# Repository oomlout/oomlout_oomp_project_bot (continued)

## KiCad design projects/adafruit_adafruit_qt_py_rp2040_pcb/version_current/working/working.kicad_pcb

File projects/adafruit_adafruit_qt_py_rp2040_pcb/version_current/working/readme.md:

# Adafruit-QT-Py-RP2040-PCB by adafruit  
This is a harvested standardized copy of a project from github.  
The original project can be found at:  
https://github.com/adafruit/Adafruit-QT-Py-RP2040-PCB  
Please consult that link for additional, details, files, and license information.  
Note: It was auto harvested and if the original repo had more than one board file or anything out of the ordinary the files here are likely not representative.

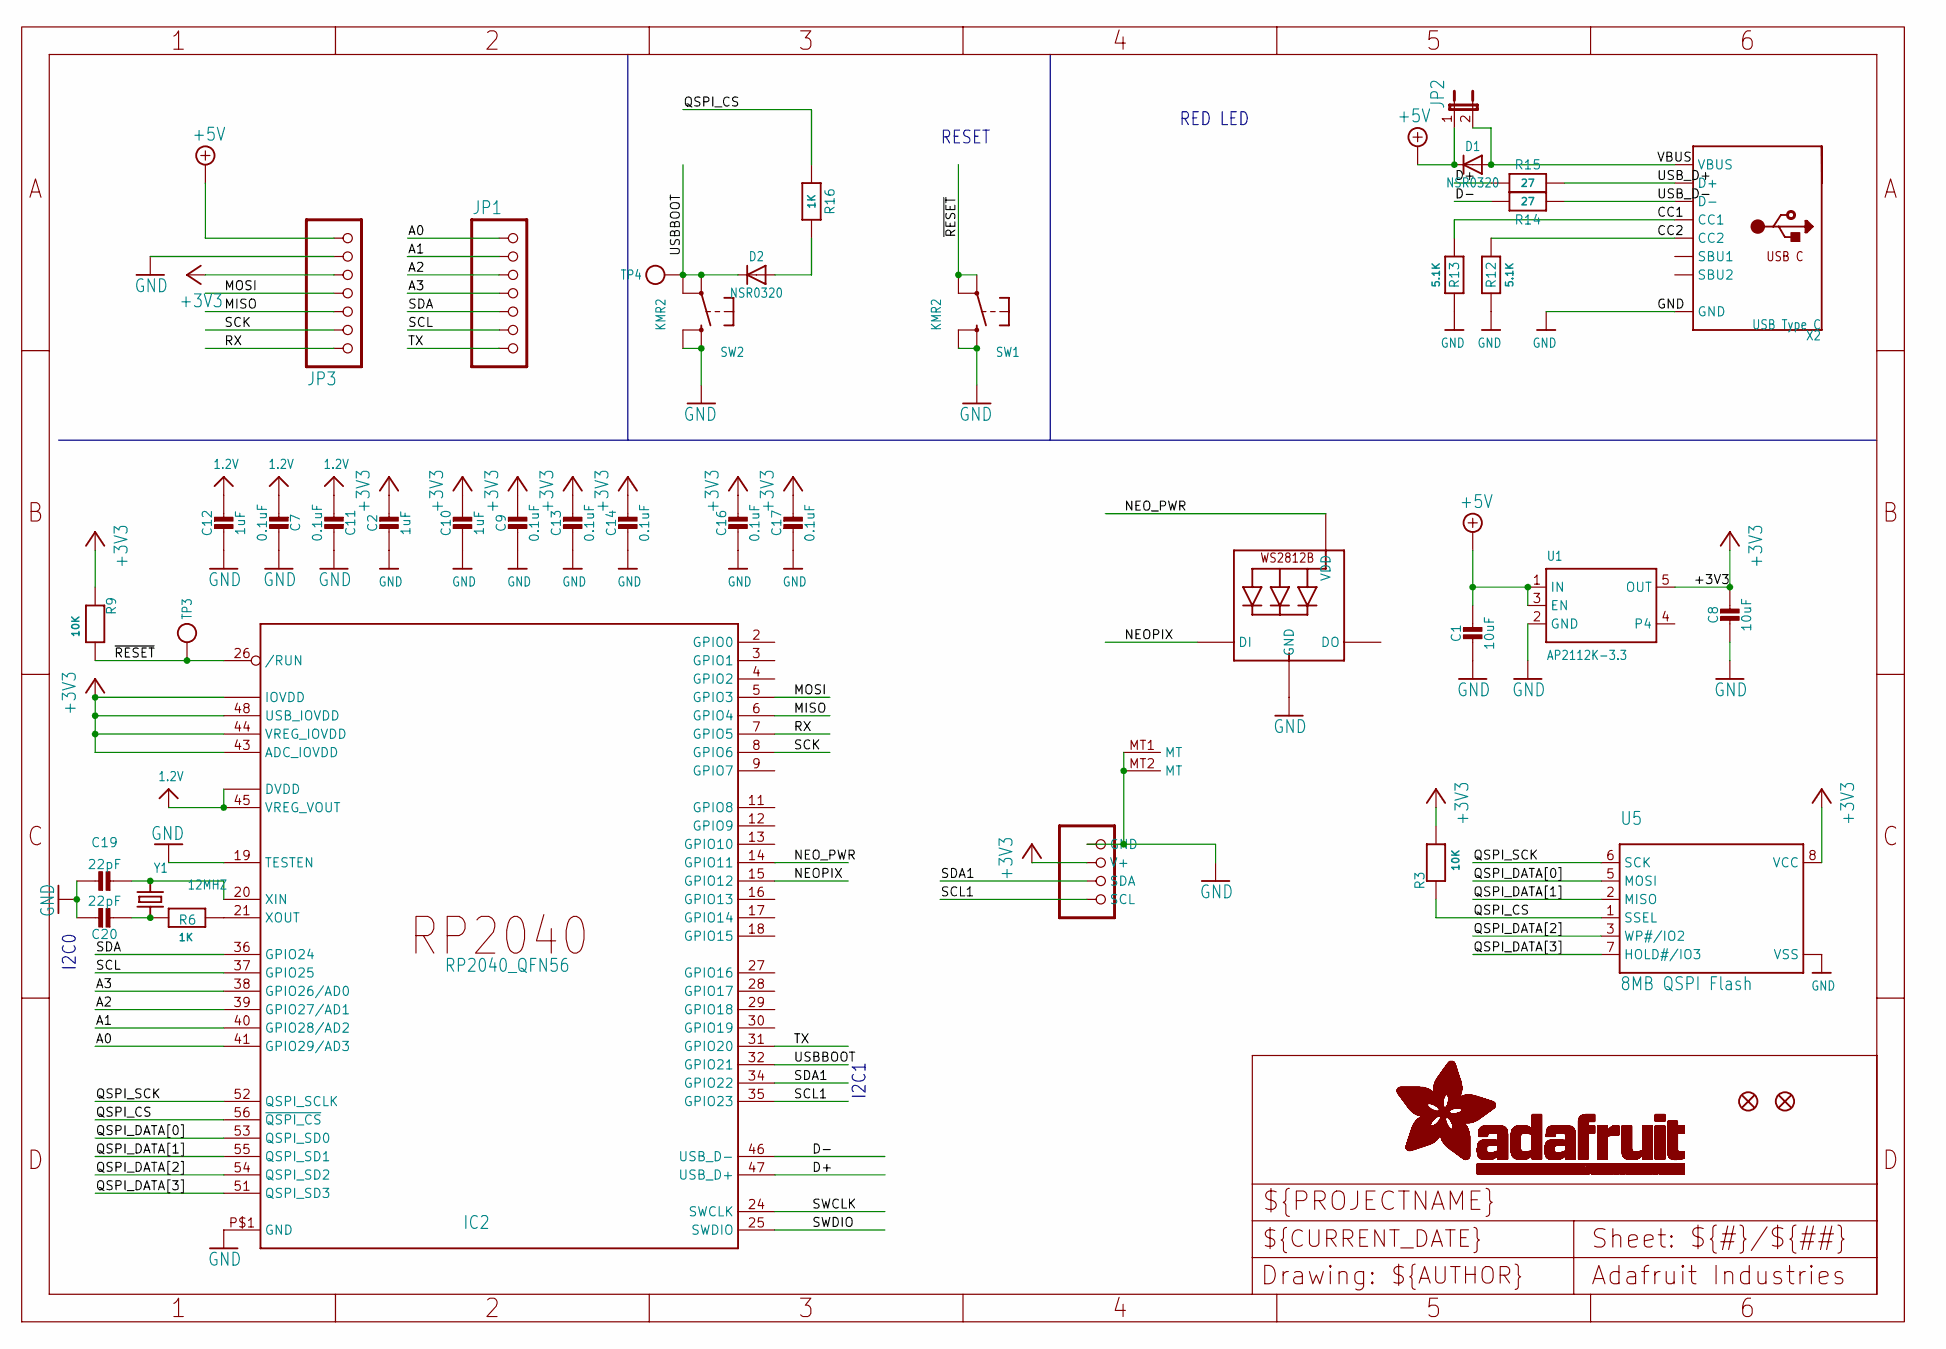
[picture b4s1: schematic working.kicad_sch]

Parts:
C1, C8: 10uF; 0805-NO
C2, C10, C12: 1uF; 0603-NO
C7, C9, C11, C13, C14, C16, C17: 0.1uF; _0402NO
C19, C20: 22pF; _0402NO
CONN1: STEMMA_I2C_QTSKINNY; JST_SH4_SKINNY
D1, D2: NSR0320; SOD-323_MINI
IC2: RP2040_QFN56; QFN56_7MM_REDUCEDEPAD
JP1, JP3: HEADER-1X7_CASTEL; 1X07_CASTEL
JP2: JUMPER-2SMD-NO; SJ_2S-NO
LED1: WS2812B_SK6805_1515; SK6805_1515
R3, R9: 10K; _0402NO
R6, R16: 1K; _0402NO
R12, R13: 5.1K; _0402NO
R14, R15: 27; _0402NO
SW1, SW2: KMR2; BTN_KMR2_4.6X2.8
TP3, TP4: TESTPOINTROUND1.5MMNO; TESTPOINT_ROUND_1.5MM_NO
U1: AP2112K-3.3; SOT23-5
U5: 8MB QSPI Flash; USON8_4X4
U$6, U$8: FIDUCIAL_1MM
X2: USB Type C; USB_C_CUSB31-CFM2AX-01-X
Y1: 12MHZ; CRYSTAL_2.5X2

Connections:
1.2V: C7.2, C11.2, C12.1, IC2.23 (DVDD), IC2.45 (VREG_VOUT), IC2.50 (DVDD)
+3V3: C2.1, C8.1, C9.1, C10.1, C13.1, C14.1, C16.1, C17.1, CONN1.2 (V+), IC2.1 (IOVDD), IC2.10 (IOVDD), IC2.22 (IOVDD), IC2.33 (IOVDD), IC2.42 (IOVDD), IC2.43 (ADC_IOVDD), IC2.44 (VREG_IOVDD), IC2.48 (USB_IOVDD), IC2.49 (IOVDD), JP3.5, JP3.5C (5), R3.2, R9.1, U1.5 (OUT), U5.8 (VCC)
+5V: C1.1, D1.C, JP2.1, JP3.7, JP3.7C (7), U1.1 (IN), U1.3 (EN)
A0: IC2.41 (GPIO29/AD3), JP1.1, JP1.1C (1)
A1: IC2.40 (GPIO28/AD2), JP1.2, JP1.2C (2)
A2: IC2.39 (GPIO27/AD1), JP1.3, JP1.3C (3)
A3: IC2.38 (GPIO26/AD0), JP1.4, JP1.4C (4)
CC1: R13.2, X2.A5 (CC1)
CC2: R12.2, X2.B5 (CC2)
D+: IC2.47 (USB_D+), R15.2
D-: IC2.46 (USB_D-), R14.2
GND: C1.2, C2.2, C7.1, C8.2, C9.2, C10.2, C11.1, C12.2, C13.2, C14.2, C16.2, C17.2, C19.1, C20.1, CONN1.1 (GND), CONN1.MT1 (MT), CONN1.MT2 (MT), IC2.19 (TESTEN), IC2.P$1 (GND), JP3.6, JP3.6C (6), LED1.4 (GND), R12.1, R13.1, SW1.B (S), SW1.B' (S1), SW2.B (S), SW2.B' (S1), U1.2 (GND), U5.4 (VSS), U5.PAD (VSS), X2.A1B12 (GND), X2.B1A12 (GND)
MISO: IC2.6 (GPIO4), JP3.3, JP3.3C (3)
MOSI: IC2.5 (GPIO3), JP3.4, JP3.4C (4)
unnamed: D2.A, R16.2
unnamed: C19.2, IC2.20 (XIN), Y1.3 (2)
unnamed: C20.2, R6.1, Y1.1
unnamed: IC2.21 (XOUT), R6.2
NEOPIX: IC2.15 (GPIO12), LED1.1 (DI)
NEO_PWR: IC2.14 (GPIO11), LED1.2 (VDD)
QSPI_CS: IC2.56 (~QSPI_CS), R3.1, R16.1, U5.1 (SSEL)
QSPI_DATA[0]: IC2.53 (QSPI_SD0), U5.5 (MOSI)
QSPI_DATA[1]: IC2.55 (QSPI_SD1), U5.2 (MISO)
QSPI_DATA[2]: IC2.54 (QSPI_SD2), U5.3 (WP#/IO2)
QSPI_DATA[3]: IC2.51 (QSPI_SD3), U5.7 (HOLD#/IO3)
QSPI_SCK: IC2.52 (QSPI_SCLK), U5.6 (SCK)
RX: IC2.7 (GPIO5), JP3.1, JP3.1C (1)
SCK: IC2.8 (GPIO6), JP3.2, JP3.2C (2)
SCL: IC2.37 (GPIO25), JP1.6, JP1.6C (6)
SCL1: CONN1.4 (SCL), IC2.35 (GPIO23)
SDA: IC2.36 (GPIO24), JP1.5, JP1.5C (5)
SDA1: CONN1.3 (SDA), IC2.34 (GPIO22)
SWCLK: IC2.24 (SWCLK)
SWDIO: IC2.25 (SWDIO)
TX: IC2.31 (GPIO20), JP1.7, JP1.7C (7)
USBBOOT: D2.C, IC2.32 (GPIO21), SW2.A, SW2.A' (P1), TP4.P$1
USB_D+: R15.1, X2.A6 (D+), X2.B6 (D+)
USB_D-: R14.1, X2.A7 (D-), X2.B7 (D-)
VBUS: D1.A, JP2.2, X2.A4B9 (VBUS), X2.B4A9 (VBUS)
~RESET: IC2.26 (/RUN), R9.2, SW1.A, SW1.A' (P1), TP3.P$1

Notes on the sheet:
I2C1
RESET
I2C0
RED LED

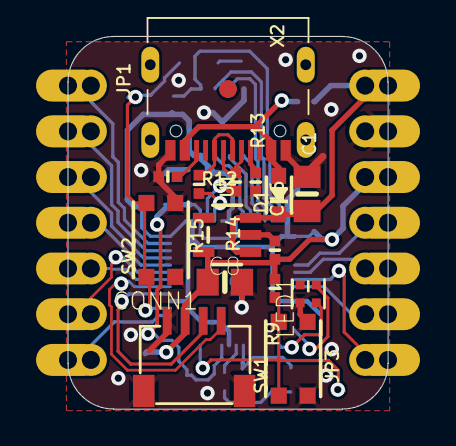
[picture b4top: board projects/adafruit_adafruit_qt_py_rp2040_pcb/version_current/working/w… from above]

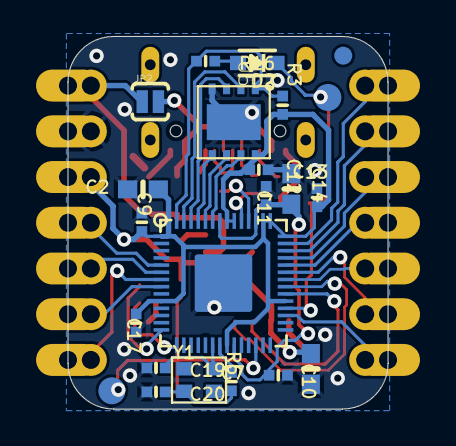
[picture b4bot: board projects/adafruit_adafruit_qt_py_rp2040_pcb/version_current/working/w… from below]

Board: 16 copper layers, 17.8 x 20.7 mm, 42 parts (23 on the bottom side), 38 nets.

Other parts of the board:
U$1: QTPICO_BOT
U$2: QTPICO_TOP

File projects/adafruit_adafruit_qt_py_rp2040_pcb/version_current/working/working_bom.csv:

Row,Description,Part,References,Value,Footprint,Quantity Per PCB,Status,Datasheet
1,,CAP_CERAMIC_0402NO,C19 C20,22pF,_0402NO,2, ,
2,,CAP_CERAMIC_0402NO,C7 C9 C11 C13 C14 C16 C17,0.1uF,_0402NO,7, ,
3,,CAP_CERAMIC0603_NO,C2 C10 C12,1uF,0603-NO,3, ,
4,,CAP_CERAMIC0805-NOOUTLINE,C1 C8,10uF,0805-NO,2, ,
5,,STEMMA_I2C_QTSKINNY,CONN1,STEMMA_I2C_QTSKINNY,JST_SH4_SKINNY,1, ,
6,,DIODE_SOD323MINI,D1 D2,NSR0320,SOD-323_MINI,2, ,
7,,RP2040_QFN56,IC2,RP2040_QFN56,QFN56_7MM_REDUCEDEPAD,1, ,
8,,HEADER-1X7_CASTEL,JP1 JP3,HEADER-1X7_CASTEL,1X07_CASTEL,2, ,
9,,JUMPER-2SMD-NO,JP2,JUMPER-2SMD-NO,SJ_2S-NO,1, ,
10,,WS2812B_SK6805_1515,LED1,WS2812B_SK6805_1515,SK6805_1515,1, ,
11,,RESISTOR_0402NO,R14 R15,27,_0402NO,2, ,
12,,RESISTOR_0402NO,R6 R16,1K,_0402NO,2, ,
13,,RESISTOR_0402NO,R12 R13,5.1K,_0402NO,2, ,
14,,RESISTOR_0402NO,R3 R9,10K,_0402NO,2, ,
15,,SWITCH_TACT_SMT4.6X2.8,SW1 SW2,KMR2,BTN_KMR2_4.6X2.8,2, ,
16,,SPIFLASH_8PIN_4X4,U5,8MB QSPI Flash,USON8_4X4,1, ,
17,,VREG_SOT23-5,U1,AP2112K-3.3,SOT23-5,1, ,
18,,USB_C,X2,USB Type C,USB_C_CUSB31-CFM2AX-01-X,1, ,
19,,CRYSTAL2.5X2.0,Y1,12MHZ,CRYSTAL_2.5X2,1, ,





Project info:
Schematic:,working
Variant:,default
Revision:,
Date:,2023-08-03_17-21-23
KiCad Version:,7.0.6-7.0.6~ubuntu22.04.1
Statistics:
Component Groups:,19
Component Count:,36 (0 SMD/ 0 THT)
Fitted Components:,36 (0 SMD/ 0 THT)
Number of PCBs:,1
Total Components:,36

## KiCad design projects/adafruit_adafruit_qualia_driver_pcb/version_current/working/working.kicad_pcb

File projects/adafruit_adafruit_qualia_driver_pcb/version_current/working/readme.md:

# Adafruit-Qualia-Driver-PCB by adafruit  
This is a harvested standardized copy of a project from github.  
The original project can be found at:  
https://github.com/adafruit/Adafruit-Qualia-Driver-PCB  
Please consult that link for additional, details, files, and license information.  
Note: It was auto harvested and if the original repo had more than one board file or anything out of the ordinary the files here are likely not representative.

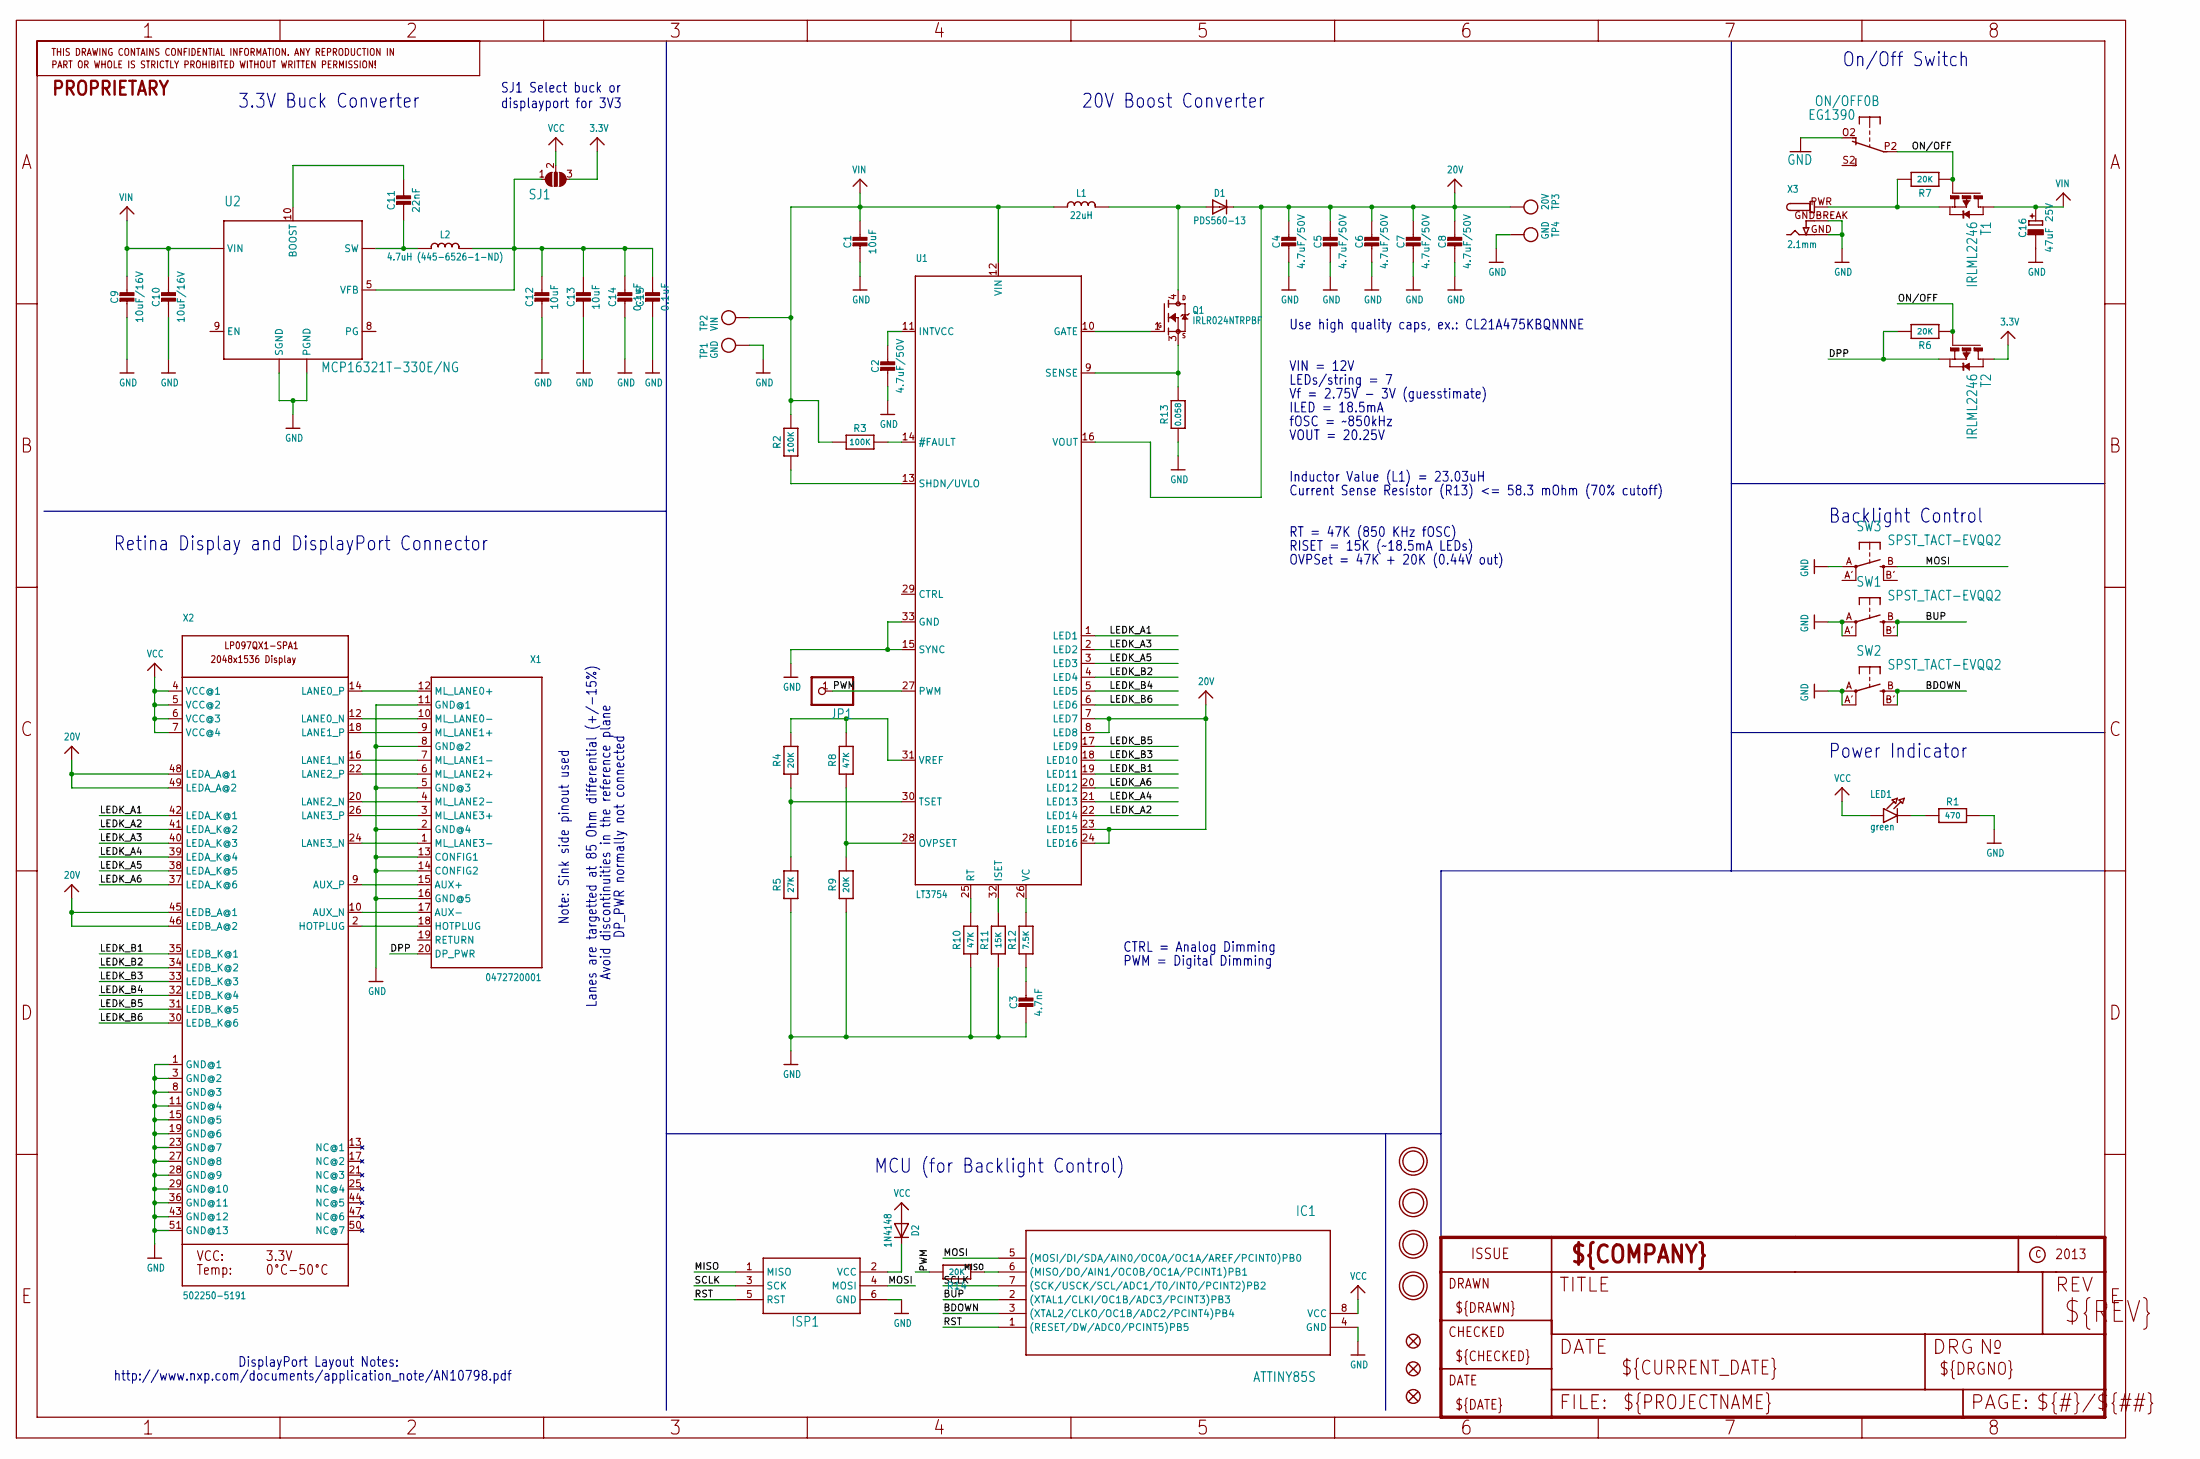
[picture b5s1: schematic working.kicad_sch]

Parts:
C1, C12, C13: 10uF; _0805
C2, C4, C5, C6, C7, C8: 4.7uF/50V; _0805
C3: 4.7nF; _0805
C9, C10: 10uF/16V; _0805
C11: 22nF; _0805
C14, C15: 0.1uF; _0805
C16: 47uF 25V; PANASONIC_C
D1: PDS560-13; POWERDI-5
D2: 1N4148; SOD-323
FID1, FID2, FID3: FIDUCIAL""; FIDUCIAL_1MM
IC1: ATTINY85S; SOIC8
ISP1: AVRISP-6; AVRISP
JP1: PINHD-1X1CB; 1X01-CLEANBIG
L1: 22uH; INDUCTOR_6X6MM_SUMIDA_CDRH5D28
L2: 4.7uH (445-6526-1-ND); INDUCTOR_5X5MM_TDK_VLC5045
LED1: green; CHIPLED_0805
ON/OFF0: EG1390
Q1: IRLR024NTRPBF; DPAK
R1: 470; _0805
R2, R3: 100K; _0805
R4, R9, R14: 20K; _0805
R5: 27K; _0805
R6, R7: 20K; _0805MP
R8, R10: 47K; _0805
R11: 15K; _0805
R12: 7.5K; _0805
R13: 0.058; 2512
SJ1: SOLDERJUMPER_2WAY; SOLDERJUMPER_2WAY_OPEN_NOPASTE
SW1, SW2, SW3: SPST_TACT-EVQQ2; EVQ-Q2
T1, T2: IRLML2246; SOT-23
TP1, TP4: GND; TESTPOINT_ROUND_1MM
TP2: VIN; TESTPOINT_ROUND_1MM
TP3: 20V; TESTPOINT_ROUND_1MM
U1: LT3754; QFN32_5MM
U2: MCP16321T-330E/NG; QFN16_3MM
U$11, U$32, U$33, U$34: MOUNTINGHOLE3.0THIN; MOUNTINGHOLE_3.0_PLATEDTHIN
X1: 0472720001; DISPLAYPORT_0472720001
X2: 502250-5191; FPC_51PIN_502250-5191_EXT
X3: 2.1mm; DCJACK_2MM_SMT

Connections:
3.3V: SJ1.3, T2.1 (D)
20V: C4.1, C5.1, C6.1, C7.1, C8.1, D1.C, TP3.P$1, U1.7 (LED7), U1.8 (LED8), U1.16 (VOUT), U1.23 (LED15), U1.24 (LED16), X2.45 (LEDB_A@1), X2.46 (LEDB_A@2), X2.48 (LEDA_A@1), X2.49 (LEDA_A@2)
AUX+: X1.15 (AUX+), X2.9 (AUX_P)
AUX-: X1.17 (AUX-), X2.10 (AUX_N)
BDOWN: IC1.3 ((XTAL2/CLKO/OC1B/ADC2/PCINT4)PB4), SW2.B (S), SW2.B' (S1)
BUP: IC1.2 ((XTAL1/CLKI/OC1B/ADC3/PCINT3)PB3), SW1.B (S), SW1.B' (S1)
DPP: R6.2, T2.2 (S), X1.20 (DP_PWR)
GND: C1.2, C2.2, C3.2, C4.2, C5.2, C6.2, C7.2, C8.2, C9.2, C10.2, C12.2, C13.2, C14.2, C15.2, C16.-, IC1.4 (GND), ISP1.6 (GND), ON/OFF0.O2 (O), R1.2, R5.1, R9.1, R10.1, R11.1, R13.1, SW1.A, SW1.A' (P1), SW2.A, SW2.A' (P1), SW3.A, TP1.P$1, TP4.P$1, U1.15 (SYNC), U1.33 (GND), U2.4 (SGND), U2.14 (PGND), U2.15 (PGND), U2.THERMAL (SGND), X1.2 (GND@4), X1.5 (GND@3), X1.8 (GND@2), X1.11 (GND@1), X1.13 (CONFIG1), X1.14 (CONFIG2), X1.16 (GND@5), X2.1 (GND@1), X2.3 (GND@2), X2.8 (GND@3), X2.11 (GND@4), X2.15 (GND@5), X2.19 (GND@6), X2.23 (GND@7), X2.27 (GND@8), X2.28 (GND@9), X2.29 (GND@10), X2.36 (GND@11), X2.43 (GND@12), X2.51 (GND@13), X3.GND, X3.GNDBREAK
HOTPLUG: X1.18 (HOTPLUG), X2.2 (HOTPLUG)
LEDK_A1: U1.1 (LED1), X2.42 (LEDA_K@1)
LEDK_A2: U1.22 (LED14), X2.41 (LEDA_K@2)
LEDK_A3: U1.2 (LED2), X2.40 (LEDA_K@3)
LEDK_A4: U1.21 (LED13), X2.39 (LEDA_K@4)
LEDK_A5: U1.3 (LED3), X2.38 (LEDA_K@5)
LEDK_A6: U1.20 (LED12), X2.37 (LEDA_K@6)
LEDK_B1: U1.19 (LED11), X2.35 (LEDB_K@1)
LEDK_B2: U1.4 (LED4), X2.34 (LEDB_K@2)
LEDK_B3: U1.18 (LED10), X2.33 (LEDB_K@3)
LEDK_B4: U1.5 (LED5), X2.32 (LEDB_K@4)
LEDK_B5: U1.17 (LED9), X2.31 (LEDB_K@5)
LEDK_B6: U1.6 (LED6), X2.30 (LEDB_K@6)
MISO: IC1.6 ((MISO/DO/AIN1/OC0B/OC1A/PCINT1)PB1), ISP1.1 (MISO), R14.1
MOSI: IC1.5 ((MOSI/DI/SDA/AIN0/OC0A/OC1A/AREF/PCINT0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), ISP1.4 (MOSI), SW3.B (S)
unnamed: X1.12 (ML_LANE0+), X2.14 (LANE0_P)
unnamed: X1.10 (ML_LANE0-), X2.12 (LANE0_N)
unnamed: X1.9 (ML_LANE1+), X2.18 (LANE1_P)
unnamed: X1.7 (ML_LANE1-), X2.16 (LANE1_N)
unnamed: X1.6 (ML_LANE2+), X2.22 (LANE2_P)
unnamed: X1.4 (ML_LANE2-), X2.20 (LANE2_N)
unnamed: X1.3 (ML_LANE3+), X2.26 (LANE3_P)
unnamed: X1.1 (ML_LANE3-), X2.24 (LANE3_N)
unnamed: C2.1, U1.11 (INTVCC)
unnamed: R2.1, U1.13 (SHDN/UVLO)
unnamed: R3.2, U1.14 (#FAULT)
unnamed: R12.2, U1.26 (VC)
unnamed: C3.1, R12.1
unnamed: LED1.C, R1.1
unnamed: R4.1, R5.2, U1.30 (TSET)
unnamed: R4.2, R8.2, U1.31 (VREF)
unnamed: R7.2, T1.2 (S), X3.PWR
unnamed: R8.1, R9.2, U1.28 (OVPSET)
unnamed: R10.2, U1.25 (RT)
unnamed: D2.C, ISP1.2 (VCC)
unnamed: R11.2, U1.32 (ISET)
unnamed: Q1.3 (S), R13.2, U1.9 (SENSE)
unnamed: Q1.1 (G), U1.10 (GATE)
unnamed: D1.A1 (A), D1.A2 (A), L1.P$2 (2), Q1.4 (D)
unnamed: C12.1, C13.1, C14.1, C15.1, L2.P$2 (2), SJ1.1, U2.5 (VFB)
unnamed: C11.1, U2.10 (BOOST)
unnamed: C11.2, L2.P$1 (1), U2.1 (SW), U2.12 (SW), U2.13 (SW), U2.16 (SW)
ON/OFF: ON/OFF0.P2, R6.1, R7.1, T1.3 (G), T2.3 (G)
PWM: JP1.1, R14.2, U1.27 (PWM)
RST: IC1.1 ((RESET/DW/ADC0/PCINT5)PB5), ISP1.5 (RST)
SCLK: IC1.7 ((SCK/USCK/SCL/ADC1/T0/INT0/PCINT2)PB2), ISP1.3 (SCK)
VCC: D2.A, IC1.8 (VCC), LED1.A, SJ1.2, X2.4 (VCC@1), X2.5 (VCC@2), X2.6 (VCC@3), X2.7 (VCC@4)
VIN: C1.1, C9.1, C10.1, C16.+, L1.P$1 (1), R2.2, R3.1, T1.1 (D), TP2.P$1, U1.12 (VIN), U2.2 (VIN), U2.3 (VIN), U2.11 (VIN)

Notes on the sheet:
MCU (for Backlight Control)
Backlight Control
RT = 47K (850 KHz fOSC)
Note: Sink side pinout used~{}
fOSC = ~850kHz
CTRL = Analog Dimming
OVPSet = 47K + 20K (0.44V out)
3.3V Buck Converter
20V Boost Converter
Avoid discontinuities in the reference plane
DP_PWR normally not connected
PWM = Digital Dimming
VIN = 12V
LEDs/string = 7
SJ1 Select buck or displayport for 3V3
ILED = 18.5mA
Retina Display and DisplayPort Connector
VOUT = 20.25V
Use high quality caps, ex.: CL21A475KBQNNNE
http://www.nxp.com/documents/application_note/AN10798.pdf
Power Indicator
Current Sense Resistor (R13) <= 58.3 mOhm (70% cutoff)
DisplayPort Layout Notes:
Lanes are targetted at 85 Ohm differential (+/-15%)
Inductor Value (L1) = 23.03uH
On/Off Switch
Vf = 2.75V - 3V (guesstimate)
RISET = 15K (~18.5mA LEDs)

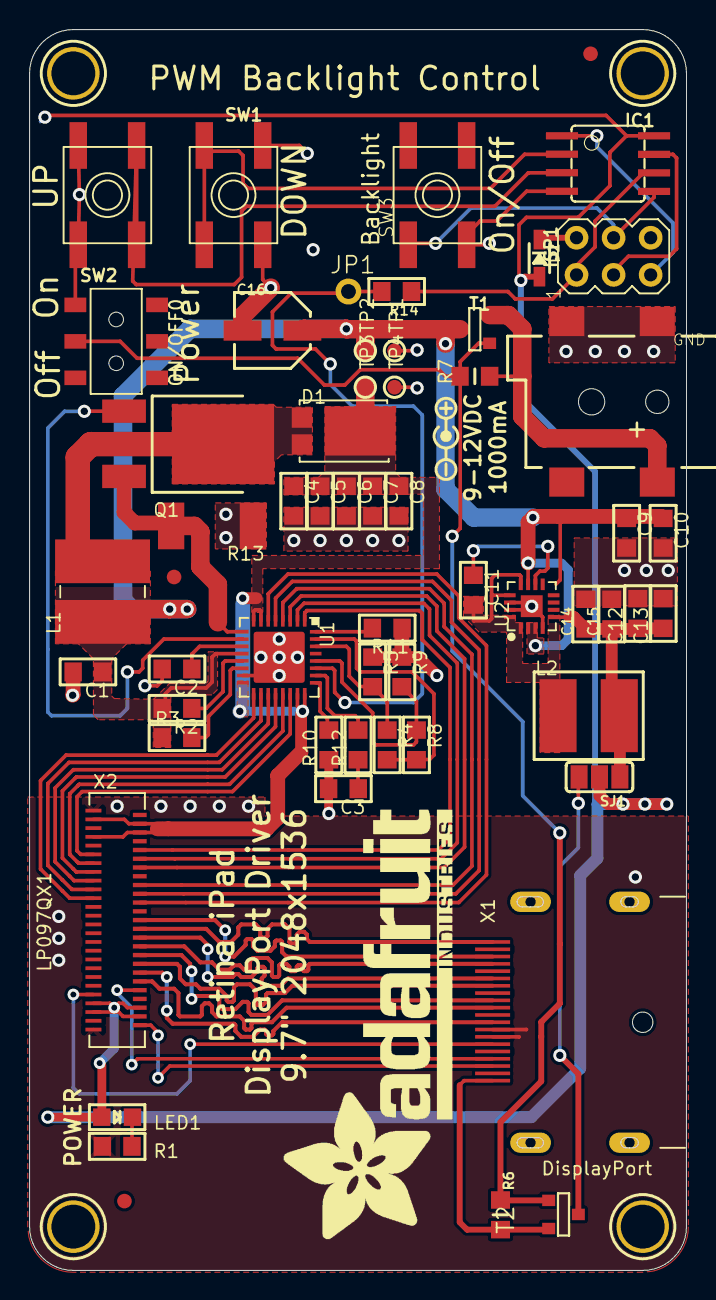
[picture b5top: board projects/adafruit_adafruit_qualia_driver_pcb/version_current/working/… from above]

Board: 2 copper layers, 45.0 x 85.0 mm, 64 parts (0 on the bottom side), 56 nets.

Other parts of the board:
U$10: SYMBOL_POSITIVE_CENTER-M
U$39: ADAFRUIT_TEXT_30MM

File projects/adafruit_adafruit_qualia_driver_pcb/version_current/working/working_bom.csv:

Row,Description,Part,References,Value,Footprint,Quantity Per PCB,Status,Datasheet
1,,CAP_CERAMIC_0805,C3,4.7nF,_0805,1, ,
2,,CAP_CERAMIC_0805,C11,22nF,_0805,1, ,
3,,CAP_CERAMIC_0805,C14 C15,0.1uF,_0805,2, ,
4,,CAP_CERAMIC_0805,C1 C12 C13,10uF,_0805,3, ,
5,,CAP_ELECTROLYTICPANASONIC_C,C16,47uF 25V,PANASONIC_C,1, ,
6,,CAP_CERAMIC_0805,C9 C10,10uF/16V,_0805,2, ,
7,,CAP_CERAMIC_0805,C2 C4 C5 C6 C7 C8,4.7uF/50V,_0805,6, ,
8,,DIODESOD-323,D2,1N4148,SOD-323,1, ,
9,,DIODEPOWERDI,D1,PDS560-13,POWERDI-5,1, ,
10,,ATTINY85S,IC1,ATTINY85S,SOIC8,1, ,
11,,AVRISP-6,ISP1,AVRISP-6,AVRISP,1, ,
12,,PINHD-1X1CB,JP1,PINHD-1X1CB,1X01-CLEANBIG,1, ,
13,,INDUCTORCDRH5D28,L1,22uH,INDUCTOR_6X6MM_SUMIDA_CDRH5D28,1, ,
14,,INDUCTORTDK_VLC5045,L2,4.7uH (445-6526-1-ND),INDUCTOR_5X5MM_TDK_VLC5045,1, ,
15,,LED0805,LED1,green,CHIPLED_0805,1, ,
16,,DPDT-EG1390,ON/OFF0,EG1390,EG1390,1, ,
17,,MOSFET-NDPAK,Q1,IRLR024NTRPBF,DPAK,1, ,
18,,RESISTOR2512,R13,0.058,2512,1, ,
19,,RESISTOR_0805,R1,470,_0805,1, ,
20,,RESISTOR_0805,R12,7.5K,_0805,1, ,
21,,RESISTOR_0805,R11,15K,_0805,1, ,
22,,RESISTOR_0805,R4 R9 R14,20K,_0805,3, ,
23,,RESISTOR_0805MP,R6 R7,20K,_0805MP,2, ,
24,,RESISTOR_0805,R5,27K,_0805,1, ,
25,,RESISTOR_0805,R8 R10,47K,_0805,2, ,
26,,RESISTOR_0805,R2 R3,100K,_0805,2, ,
27,,SPST_TACT-EVQQ2,SW1 SW2 SW3,SPST_TACT-EVQQ2,EVQ-Q2,3, ,
28,,PMOSSOT23,T1 T2,IRLML2246,SOT-23,2, ,
29,,VREG_LT3754,U1,LT3754,QFN32_5MM,1, ,
30,,VREG_MCP16321/2,U2,MCP16321T-330E/NG,QFN16_3MM,1, ,
31,,DISPLAYPORTSINKSIDE,X1,0472720001,DISPLAYPORT_0472720001,1, ,
32,,DCBARRELSMT_CORRECT,X3,2.1mm,DCJACK_2MM_SMT,1, ,
33,,DISP_DISPLAYPORT_LP097QX1-SPA1HANDSOLDERING,X2,502250-5191,FPC_51PIN_502250-5191_EXT,1, ,





Project info:
Schematic:,working
Variant:,default
Revision:,
Date:,2023-08-03_17-21-23
KiCad Version:,7.0.6-7.0.6~ubuntu22.04.1
Statistics:
Component Groups:,33
Component Count:,50 (0 SMD/ 0 THT)
Fitted Components:,50 (0 SMD/ 0 THT)
Number of PCBs:,1
Total Components:,50

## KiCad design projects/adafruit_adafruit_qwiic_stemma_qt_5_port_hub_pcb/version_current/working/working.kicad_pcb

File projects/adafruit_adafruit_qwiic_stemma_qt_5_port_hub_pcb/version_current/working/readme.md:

# Adafruit-Qwiic-Stemma-QT-5-Port-Hub-PCB by adafruit  
This is a harvested standardized copy of a project from github.  
The original project can be found at:  
https://github.com/adafruit/Adafruit-Qwiic-Stemma-QT-5-Port-Hub-PCB  
Please consult that link for additional, details, files, and license information.  
Note: It was auto harvested and if the original repo had more than one board file or anything out of the ordinary the files here are likely not representative.

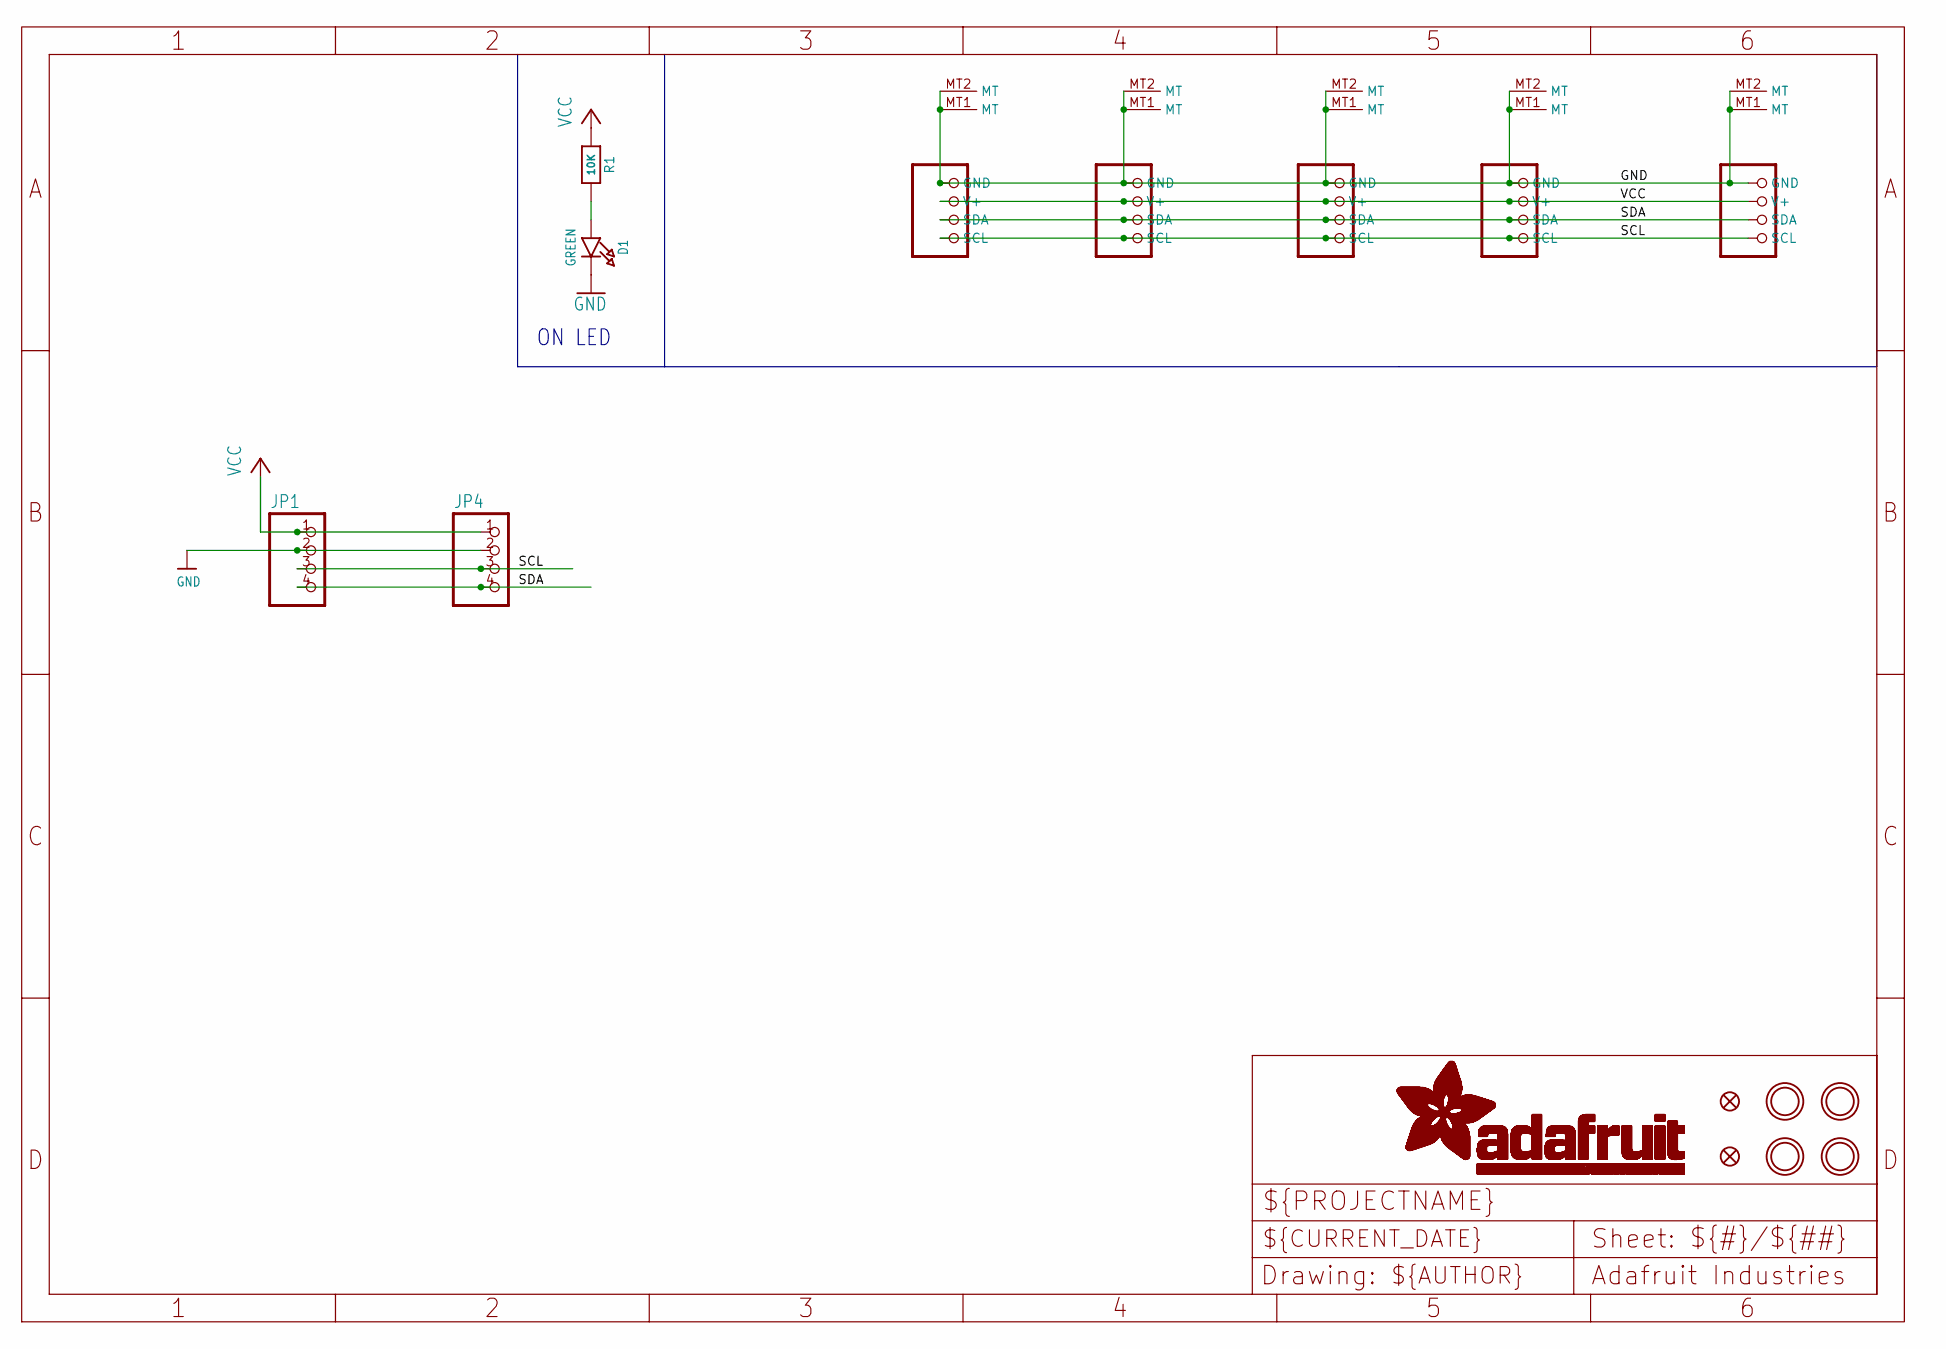
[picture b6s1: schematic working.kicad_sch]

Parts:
CONN1, CONN2, CONN3, CONN4, CONN5: STEMMA_I2C_QTRA; JST_SH4_RA
D1: GREEN; CHIPLED_0603_NOOUTLINE
FID3, FID4: FIDUCIAL_1MM
JP1, JP4: HEADER-1X476MIL; 1X04_ROUND_76
R1: 10K; 0603-NO
U$1, U$17, U$19, U$21: MOUNTINGHOLE2.5; MOUNTINGHOLE_2.5_PLATED

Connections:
GND: CONN1.1 (GND), CONN1.MT1 (MT), CONN1.MT2 (MT), CONN2.1 (GND), CONN2.MT1 (MT), CONN2.MT2 (MT), CONN3.1 (GND), CONN3.MT1 (MT), CONN3.MT2 (MT), CONN4.1 (GND), CONN4.MT1 (MT), CONN4.MT2 (MT), CONN5.1 (GND), CONN5.MT1 (MT), CONN5.MT2 (MT), D1.C, JP1.2, JP4.2
unnamed: D1.A, R1.2
SCL: CONN1.4 (SCL), CONN2.4 (SCL), CONN3.4 (SCL), CONN4.4 (SCL), CONN5.4 (SCL), JP1.3, JP4.3
SDA: CONN1.3 (SDA), CONN2.3 (SDA), CONN3.3 (SDA), CONN4.3 (SDA), CONN5.3 (SDA), JP1.4, JP4.4
VCC: CONN1.2 (V+), CONN2.2 (V+), CONN3.2 (V+), CONN4.2 (V+), CONN5.2 (V+), JP1.1, JP4.1, R1.1

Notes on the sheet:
ON LED

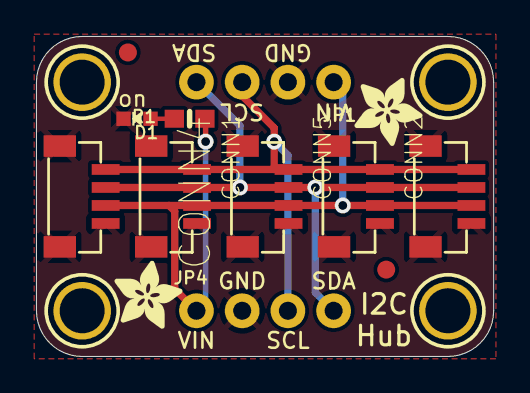
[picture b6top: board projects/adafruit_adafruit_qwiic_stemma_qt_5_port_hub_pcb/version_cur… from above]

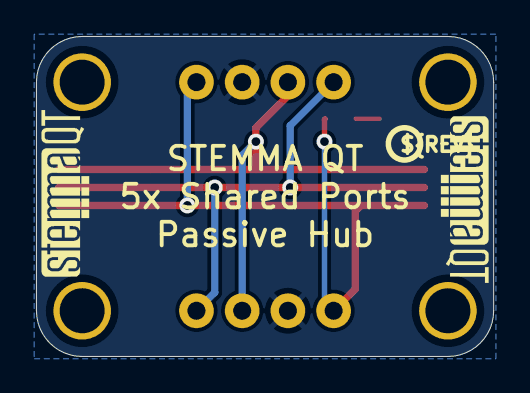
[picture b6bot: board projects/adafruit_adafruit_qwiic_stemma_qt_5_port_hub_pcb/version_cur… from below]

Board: 2 copper layers, 25.4 x 17.8 mm, 20 parts (3 on the bottom side), 5 nets.

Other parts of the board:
U$2, U$3: ADAFRUIT_3.5MM
U$25: PCBFEAT-REV-040
U$30, U$31: STEMMAQT
